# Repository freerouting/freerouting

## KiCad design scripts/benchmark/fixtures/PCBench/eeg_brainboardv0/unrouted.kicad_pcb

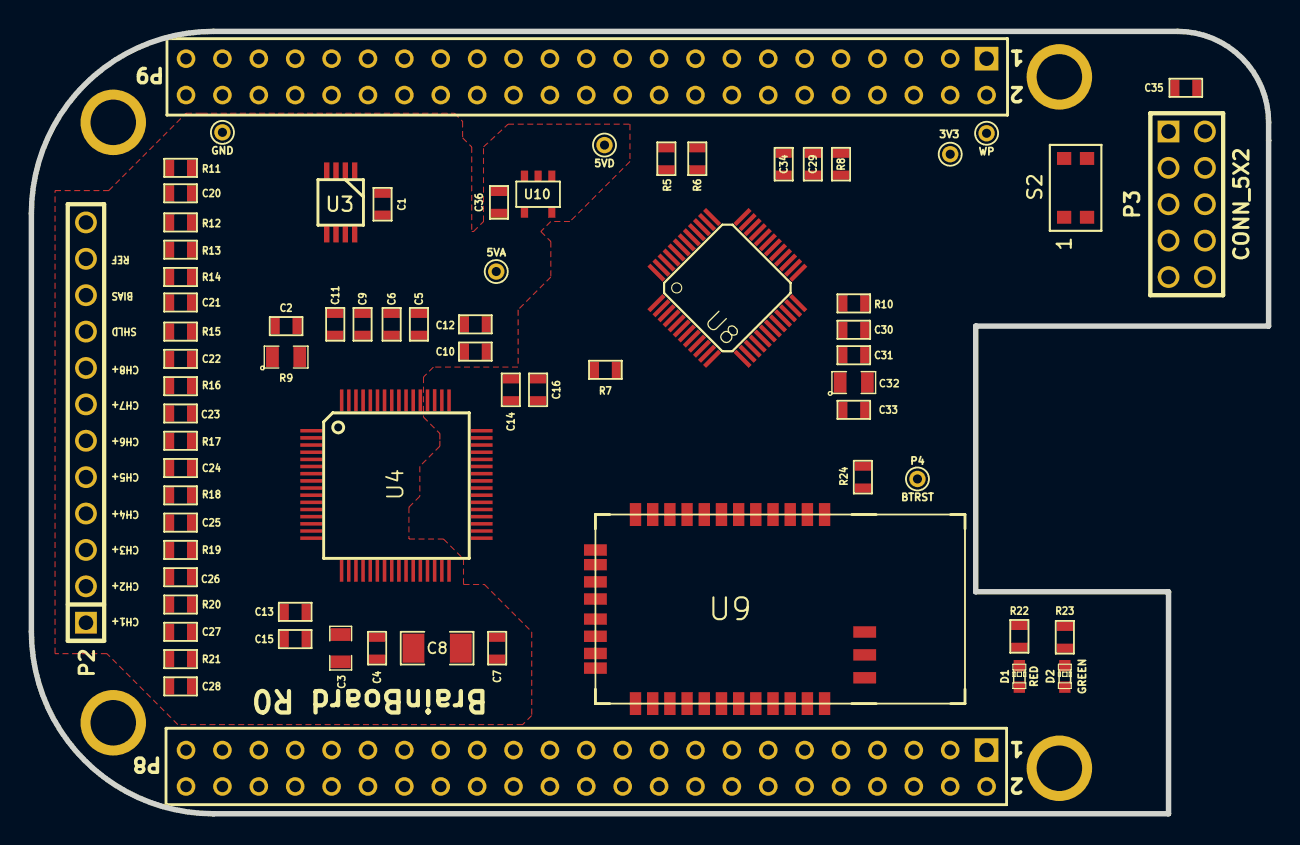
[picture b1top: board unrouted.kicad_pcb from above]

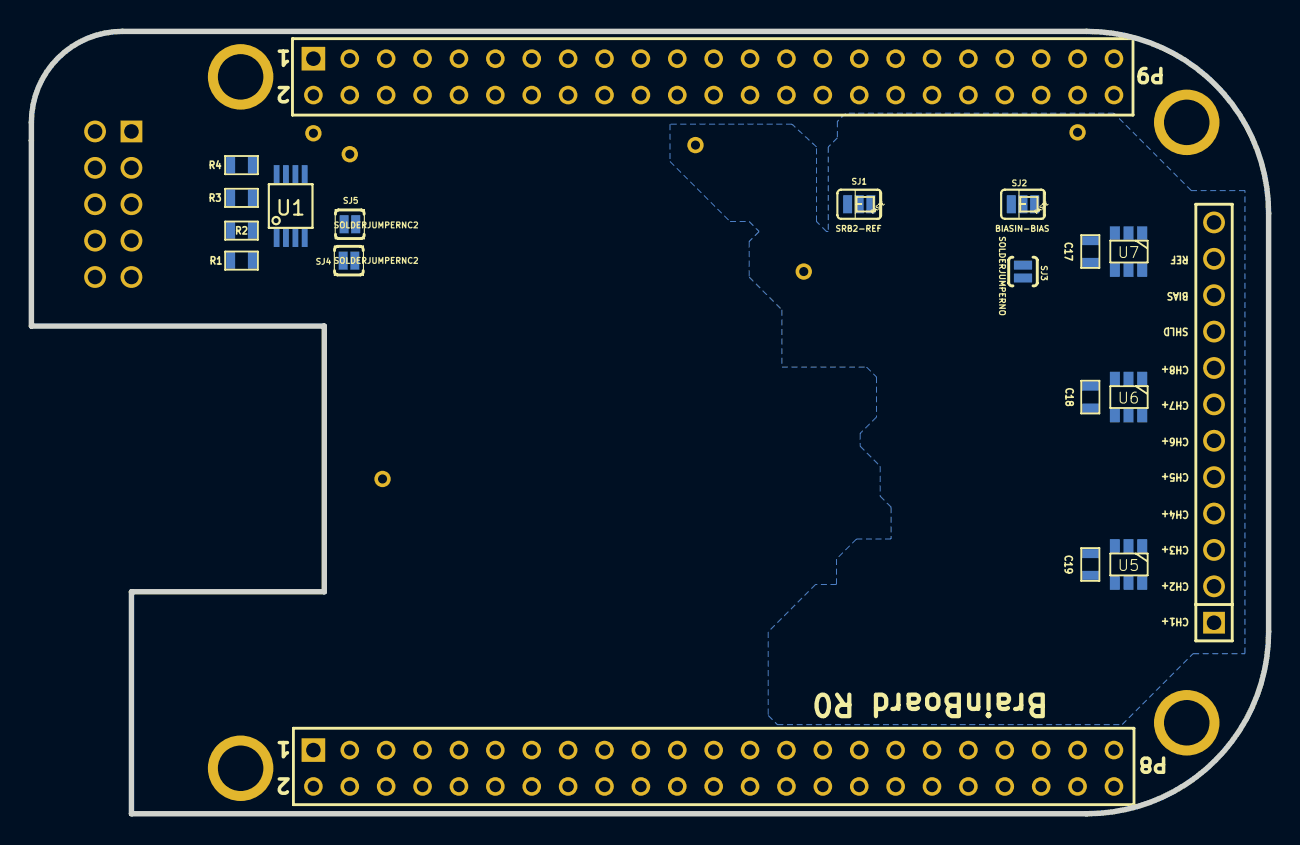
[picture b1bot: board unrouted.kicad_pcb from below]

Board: 4 copper layers, 86.4 x 54.6 mm, 86 parts (16 on the bottom side), 70 nets, no tracks yet.

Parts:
C1, C6, C11, C12, C15, C16, C17, C18, C19, C29, C31, C33, C34, C35, C36: 0.1uF; SM0603
C2: 1nF; SM0603
C3, C32: 10uF; SM0805
C4, C5, C7, C9, C10, C13, C14: 1uF; SM0603
C8: 100uF; SM1206
C20, C21, C22, C23, C24, C25, C26, C27, C28: 4.7nF; SM0603
C30: 2.2uF; SM0603
D1: RED; LED-0603
D2: GREEN; LED-0603
P1: WP; PINTST
P2: CONN_12; PIN_ARRAY-12X1
P3: CONN_5X2; PIN_ARRAY_5x2
P4: BTRST; PINTST
P5: GND; PINTST
P6: 5VD; PINTST
P7: 3V3; PINTST
P8: 5VA; PINTST
R1, R2, R3: 4.7K; SM0603
R4, R7, R8, R10, R24: 10K; SM0603
R5, R6: 5.6K; SM0603
R9: 499K,0.1%; SM0805
R11, R12, R13, R14, R15, R16, R17, R18, R19, R20, R21: 4.99K; SM0603
R22, R23: 330; SM0603
S2: SMT_BUTTON; KMR231GLFS
SJ1, SJ2: SOLDERJUMPER_2WAYPASTE2&3; SparkFun-Passives-SJ_3_PASTE2&3
SJ3: SOLDERJUMPERNO; SparkFun-Passives-SJ_2S-NO
SJ4, SJ5: SOLDERJUMPERNC2; SparkFun-Passives-SJ_2S-NOTRACE
U1: 24C256; SSOP8
U2: BEAGLEBONE_BLACK
U3: OPA2376; MSOP_8
U4: ADS1299; TQFP_64
U5, U6, U7: TPD4E001; SOT23_6
U8: ATUC3L064; -TQFP48
U9: BLUETOOTH-RN42; SparkFun-RF-RN41
U10: TPS73150; SOT23-5

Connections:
3V3: C14.1, C16.1, C29.1, C30.1, C31.1, C32.1, C33.1, C34.1, C35.1, P3.4, P7.1, R1.1, R2.1, R3.1, R4.1, R5.1, R6.1, R7.1, R8.1, R10.1, U1.8, U2.B3, U2.B4, U4.48, U4.50, U4.52, U8.17, U8.18, U8.34, U8.35, U8.42, U8.48, U9.11
+5VA: C1.1, C9.1, C10.1, C11.1, C12.1, C13.1, C15.1, C17.1, C18.1, C19.1, P8.1, U3.8, U4.19, U4.21, U4.22, U4.54, U4.56, U4.59, U5.6, U6.6, U7.6, U10.5
+5VD: P6.1, U2.B7, U2.B8, U10.1, U10.3
/A0: R3.2, U1.1
/A1: R2.2, SJ5.1, U1.2
/A2: R1.2, SJ4.1, U1.3
/BrainBoard AFE/BIASIN: SJ2.1, U4.62
/BrainBoard AFE/BIASINV: C2.1, R9.2, U4.61
/BrainBoard AFE/BIASOUT: C2.2, R9.1, SJ3.2, U4.63
/BrainBoard AFE/SRB1: U3.6, U3.7, U4.17
/BrainBoard AFE/SRB2: SJ1.1, U4.18
/BrainBoard AFE/VCAP1: C8.1, U4.28
/BrainBoard AFE/VCAP2: C7.1, U4.30
/BrainBoard AFE/VCAP3: C5.1, C6.1, U4.55
/BrainBoard AFE/VCAP4: C4.1, U4.26
/BrainBoard AFE/VREFP: C3.2, U4.24
/BrainBoard Analog In/BIAS_ELEC: P2.10, R12.1, U7.2
/BrainBoard Analog In/BIAS_SHD: P2.9, R13.1, U7.4
/BrainBoard Analog In/CH1ELEC_P: P2.1, R21.1, U5.4
/BrainBoard Analog In/CH2ELEC_P: P2.2, R20.1, U5.5
/BrainBoard Analog In/CH3ELEC_P: P2.3, R19.1, U5.1
/BrainBoard Analog In/CH4ELEC_P: P2.4, R18.1, U5.2
/BrainBoard Analog In/CH5ELEC_P: P2.5, R17.1, U6.4
/BrainBoard Analog In/CH6ELEC_P: P2.6, R16.1, U6.5
/BrainBoard Analog In/CH7ELEC_P: P2.7, R15.1, U6.1
/BrainBoard Analog In/CH8ELEC_P: P2.8, R14.1, U6.2
/BrainBoard Analog In/REF_ELEC: P2.11, R11.1, U7.1
/BrainBoard Bluetooth/FACTORY: P4.1, R24.1, U9.22
/BrainBoard Bluetooth/STATUS: D2.1, U9.19
/BrainBoard Bluetooth/STATUSn: D1.1, U9.21
/BrainBoard MCU/RESET_MCU: P3.6, U8.22
/BrainBoard MCU/TCK: P3.1, U8.11
/BrainBoard MCU/TDI: P3.9, U8.4
/BrainBoard MCU/TDO: P3.3, U8.13
/BrainBoard MCU/TMS: P3.5, U8.14
/CS: R7.2, U4.39, U8.6
/DRDY: U4.47, U8.31
/PWDN: R8.2, U4.35, U8.25
/RESET: R10.2, U4.36, U8.21
/SCL: R5.2, U1.6, U2.B19
/SDA: R6.2, U1.5, U2.B20
/WP: P1.1, R4.2, U1.7
AGND: C1.2, C3.1, C4.2, C5.2, C6.2, C7.2, C8.2, C9.2, C10.2, C11.2, C12.2, C13.2, C14.2, C15.2, C16.2, C17.2, C18.2, C19.2, C20.2, C21.2, C22.2, C23.2, C24.2, C25.2, C26.2, C27.2, C28.2, C29.2, C30.2, C31.2, C32.2, C33.2, C34.2, C35.2, C36.2, P3.2, P3.10, P5.1, R22.2, R23.2, R24.2, S2.1, S2.3, SJ4.2, SJ5.2, U1.4, U2.A1, U2.A2, U2.B1, U2.B2, U2.B34, U2.B43, U2.B44, U2.B45, U2.B46, U3.4, U4.20, U4.23, U4.25, U4.31, U4.32, U4.33, U4.49, U4.51, U4.53, U4.57, U4.58, U5.3, U6.3, U7.3, U8.1, U8.19, U8.33, U8.43, U8.45, U9.1, U9.12, U9.25, U9.27, U9.28, U9.29, U10.2
AIN1P: C28.1, R21.2, U4.16
AIN2P: C27.1, R20.2, U4.14
AIN3P: C26.1, R19.2, U4.12
AIN4P: C25.1, R18.2, U4.10
AIN5P: C24.1, R17.2, U4.8
AIN6P: C23.1, R16.2, U4.6
AIN7P: C22.1, R15.2, U4.4
AIN8P: C21.1, R14.2, U4.2
BIAS: R12.2, SJ2.3, U3.3
MISO: U4.43, U8.7
MOSI: U4.34, U8.8
unnamed: S2.2, S2.4, U2.B9
unnamed: SJ2.2, SJ3.1
unnamed: SJ1.2, U3.5
unnamed: D2.2, R23.1
unnamed: D1.2, R22.1
unnamed: C36.1, U10.4
REF: C20.1, R11.2, SJ1.3
RESET_BT: U8.30, U9.5
SCLK: U4.40, U8.16
SHIELD: R13.2, U3.1, U3.2
START: U4.38, U8.39
SYS_RESETn: U2.B10, U8.20
UARTBT_RX: U2.A37, U9.13
UARTBT_TX: U2.A38, U9.14
UARTUC_RX: U2.B13, U8.15
UARTUC_TX: U2.B11, U8.10

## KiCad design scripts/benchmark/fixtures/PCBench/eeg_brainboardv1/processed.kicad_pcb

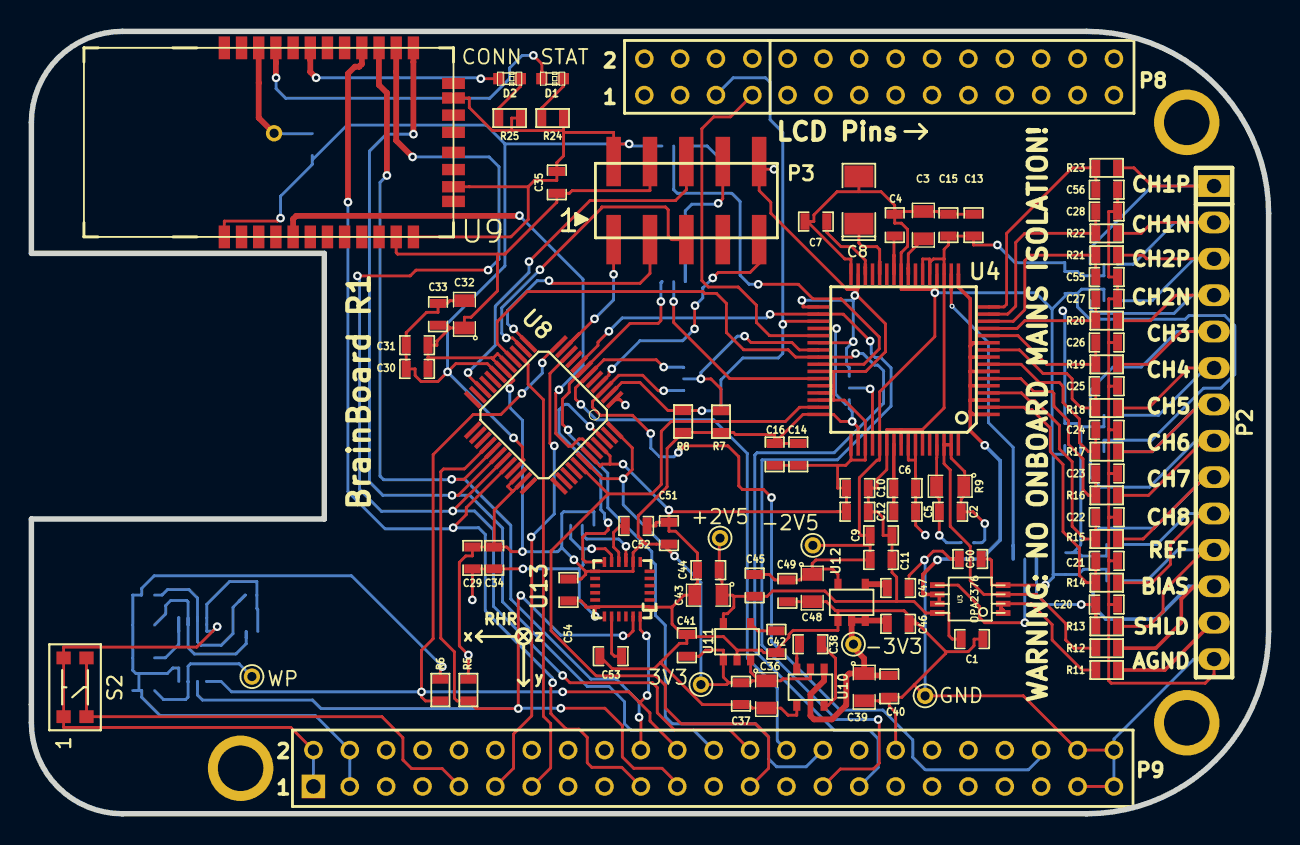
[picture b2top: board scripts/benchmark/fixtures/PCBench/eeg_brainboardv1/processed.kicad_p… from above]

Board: 4 copper layers, 86.4 x 54.6 mm, 116 parts (0 on the bottom side), 86 nets.

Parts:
C1, C6, C11, C12, C15, C16, C17, C18, C19, C29, C31, C33, C34, C35, C45, C50, C51, C52: 0.1uF; SM0603_Capa
C2: 1nF; SM0603_Capa
C3, C32, C36, C39, C43, C48: 10uF; SM0805
C4, C5, C7, C9, C10, C13, C14, C37, C38, C40, C41, C46: 1uF; SM0603_Capa
C8: 100uF; SM1206POL
C20, C21, C22, C23, C24, C25, C26, C27, C28, C55, C56: 4.7nF; SM0603_Capa
C30, C44, C49: 2.2uF; SM0603_Capa
C42, C47, C54: 0.01uF; SM0603_Capa
C53: 2.2nF; SM0603_Capa
D1: STAT; LED-0603
D2: CONN; LED-0603
P1: WP; PINTST
P2: CONN_14; pin_strip_14
P3: CONN_5X2; bb02-hp10
P4: BTRST; PINTST
P5: GND; PINTST
P6: -3V3; PINTST
P7: 3V3; PINTST
P8: +2V5; PINTST
P9: -2V5; PINTST
P10: CONN_2X2; bb02-hp04
R1, R2, R3: 4.7K; SM0603
R4, R7, R8, R26: 10K; SM0603
R5, R6: 5.6K; SM0603
R9: 499K,0.1%; SM0805
R11, R12, R13, R14, R15, R16, R17, R18, R19, R20, R21, R22, R23: 4.99K; SM0603
R24, R25: 330; SM0603
S2: SMT_BUTTON; KMR231GLFS
SJ1: REF-SRB2; SparkFun-Passives-SJ_3_PASTE2&3
SJ2, SJ7: DAISY_CS; SparkFun-Passives-SJ_3_PASTE2&3
SJ3: NO BIAS FILT; SparkFun-Passives-SJ_2S-NO
SJ4: A2; SparkFun-Passives-SJ_2S-NOTRACE
SJ5: A1; SparkFun-Passives-SJ_2S-NOTRACE
SJ6: DAISY_OUT; SparkFun-Passives-SJ_3_PASTE2&3
SJ8: CLKSEL; SparkFun-Passives-SJ_3_PASTE1&2
SJ9: I2C Address Select (2&3NC); SparkFun-Passives-SJ_3_PASTE2&3
U1: 24C256; SSOP8
U2: BEAGLEBONE_BLACK; BEAGLEBONE_BLACK_EEGMOD
U3: OPA2376; msoic-8
U4: ADS1299; TQFP_64
U5, U6, U7: TPD4E001DBV; SOT23_6
U8: ATUC3L064; -TQFP48
U9: BLUETOOTH-RN42; SparkFun-RF-RN41
U10: TPS60403; SOT23-5
U11: TPS73225; SOT23-5
U12: TPS72325; SOT23-5
U13: MPU6050; QFN24-4x4

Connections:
+2.5V: C1.1, C9.1, C10.1, C11.1, C12.1, C13.1, C15.1, C17.1, C18.1, C19.1, C43.1, C44.1, C45.1, P8.1, U3.8, U4.19, U4.21, U4.22, U4.54, U4.56, U4.59, U5.5, U6.5, U7.5, U11.5
+3.3V: C14.1, C16.1, C29.1, C30.1, C31.1, C32.1, C33.1, C34.1, C35.1, C36.1, C37.1, C41.1, C51.1, C54.1, P3.4, P7.1, R1.1, R2.1, R3.1, R4.1, R5.1, R6.1, R7.1, R8.1, SJ8.1, SJ9.1, U1.8, U2.B3, U2.B4, U4.36, U4.48, U4.50, U8.17, U8.18, U8.34, U8.35, U8.42, U8.48, U9.11, U10.2, U11.1, U11.3, U13.8, U13.13
-2.5V: C3.1, C4.2, C5.2, C6.2, C7.2, C8.2, C9.2, C11.2, C13.2, C15.2, C17.2, C18.2, C19.2, C45.2, C48.1, C49.1, C50.1, P9.1, U3.4, U4.20, U4.23, U4.25, U4.32, U4.53, U4.57, U4.58, U5.2, U6.2, U7.2, U12.5
-3.3V: C39.1, C40.1, C46.1, P6.1, U10.1, U12.2, U12.3
/A0: R3.2, U1.1
/A1: R2.2, SJ5.1, U1.2
/A2: R1.2, SJ4.1, U1.3
/BrainBoard AFE//CS: R7.2, SJ2.2, U4.39
/BrainBoard AFE/BIASINV: C2.1, R9.2, SJ3.1, U4.61
/BrainBoard AFE/CLKSEL: SJ8.2, U4.52
/BrainBoard AFE/DAISY: SJ7.2, U4.41
/BrainBoard AFE/DAISY_IN: P10.1, SJ7.1
/BrainBoard AFE/DOUT: SJ6.2, U4.43
/BrainBoard AFE/SRB1: U3.6, U3.7, U4.1, U4.3, U4.5, U4.7, U4.9, U4.11, U4.17
/BrainBoard AFE/SRB2: SJ1.1, U4.18
/BrainBoard AFE/VCAP1: C8.1, U4.28
/BrainBoard AFE/VCAP2: C7.1, U4.30
/BrainBoard AFE/VCAP3: C5.1, C6.1, U4.55
/BrainBoard AFE/VCAP4: C4.1, U4.26
/BrainBoard AFE/VREFP: C3.2, U4.24
/BrainBoard Analog In/BIAS_ELEC: P2.12, R12.1, U7.3
/BrainBoard Analog In/BIAS_SHD: P2.13, R11.1
/BrainBoard Analog In/CH1ELEC_N: P2.2, R22.1, U5.6
/BrainBoard Analog In/CH1ELEC_P: P2.1, R23.1, U5.4
/BrainBoard Analog In/CH2ELEC_N: P2.4, R20.1, U5.3
/BrainBoard Analog In/CH2ELEC_P: P2.3, R21.1, U5.1
/BrainBoard Analog In/CH3ELEC_P: P2.5, R19.1, U6.4
/BrainBoard Analog In/CH4ELEC_P: P2.6, R18.1, U6.6
/BrainBoard Analog In/CH5ELEC_P: P2.7, R17.1, U6.1
/BrainBoard Analog In/CH6ELEC_P: P2.8, R16.1, U6.3
/BrainBoard Analog In/CH7ELEC_P: P2.9, R15.1, U7.4
/BrainBoard Analog In/CH8ELEC_P: P2.10, R14.1, U7.6
/BrainBoard Analog In/REF_ELEC: P2.11, R13.1, U7.1
/BrainBoard Bluetooth/FACTORY: P4.1, R26.1, U9.22
/BrainBoard Bluetooth/STATUS: D2.1, U9.19
/BrainBoard Bluetooth/STATUSn: D1.1, U9.21
/BrainBoard IMU/AD0: SJ9.2, U13.9
/BrainBoard IMU/CPOUT: C53.1, U13.20
/BrainBoard IMU/REGOUT: C52.1, U13.10
/BrainBoard MCU/RESET_MCU: P3.6, U8.22
/BrainBoard MCU/TCK: P3.1, U8.11
/BrainBoard MCU/TDI: P3.9, U8.4
/BrainBoard MCU/TDO: P3.3, U8.13
/BrainBoard MCU/TMS: P3.5, U8.14
/CS_DAISY: SJ2.1, U2.B42, U8.3
/CS_MAIN: SJ2.3, U2.B28, U8.6
/DRDY: U2.B25, U4.47, U8.41
/PWDN: R8.2, U2.A23, U4.35, U8.2
/WP: P1.1, R4.2, U1.7
AGND: C1.2, C10.2, C12.2, C14.2, C16.2, C20.2, C21.2, C22.2, C23.2, C24.2, C25.2, C26.2, C27.2, C28.2, C29.2, C30.2, C31.2, C32.2, C33.2, C34.2, C35.2, C36.2, C37.2, C39.2, C40.2, C41.2, C42.2, C43.2, C44.2, C46.2, C47.2, C48.2, C49.2, C50.2, C51.2, C52.2, C53.2, C54.2, C55.2, C56.2, P2.14, P3.2, P3.10, P5.1, R24.2, R25.2, R26.2, S2.1, S2.3, SJ4.2, SJ5.2, SJ7.3, SJ8.3, SJ9.3, U1.4, U2.B1, U2.B2, U2.B34, U2.B43, U2.B44, U2.B45, U2.B46, U4.31, U4.33, U4.38, U4.42, U4.44, U4.45, U4.46, U4.49, U4.51, U8.1, U8.19, U8.33, U8.43, U8.45, U9.1, U9.12, U9.28, U9.29, U10.4, U11.2, U12.1, U13.1, U13.11, U13.18
AIN1N: C28.1, R22.2, U4.15
AIN1P: C56.1, R23.2, U4.16
AIN2N: C27.1, R20.2, U4.13
AIN2P: C55.1, R21.2, U4.14
AIN3P: C26.1, R19.2, U4.12
AIN4P: C25.1, R18.2, U4.10
AIN5P: C24.1, R17.2, U4.8
AIN6P: C23.1, R16.2, U4.6
AIN7P: C22.1, R15.2, U4.4
AIN8P: C21.1, R14.2, U4.2
BIAS: C2.2, R9.1, R12.2, SJ3.2, U3.3, U4.62, U4.63
CLK: U2.A25, U4.37
DAISY_OUT: P3.8, SJ6.1
I2C2_SCL: R5.2, U1.6, U2.B21, U8.28, U13.23
I2C2_SDA: R6.2, U1.5, U2.B22, U8.12, U13.24
IMU_INT: U8.46, U13.12
MISO: SJ6.3, U2.B30, U8.7
MOSI: U2.B29, U4.34, U8.8
unnamed: S2.2, S2.4, U2.B9
unnamed: D2.2, R25.1
unnamed: D1.2, R24.1
unnamed: C47.1, U12.4
unnamed: C38.1, U10.5
unnamed: C38.2, U10.3
unnamed: C42.1, U11.4
unnamed: SJ1.2, U3.5
REF: C20.1, R13.2, SJ1.3
RESET_BT: U8.44, U9.5
SCLK: U2.B31, U4.40, U8.16
SHIELD: R11.2, U3.1, U3.2
UARTBT_CTS: U2.B20, U8.29, U9.15
UARTBT_RTS: U2.B19, U8.32, U9.16
UARTBT_RX: U2.B26, U8.31, U9.14
UARTBT_TX: U2.B24, U8.30, U9.13
UARTUC_RX: U2.B13, U8.15
UARTUC_TX: U2.B11, U8.10

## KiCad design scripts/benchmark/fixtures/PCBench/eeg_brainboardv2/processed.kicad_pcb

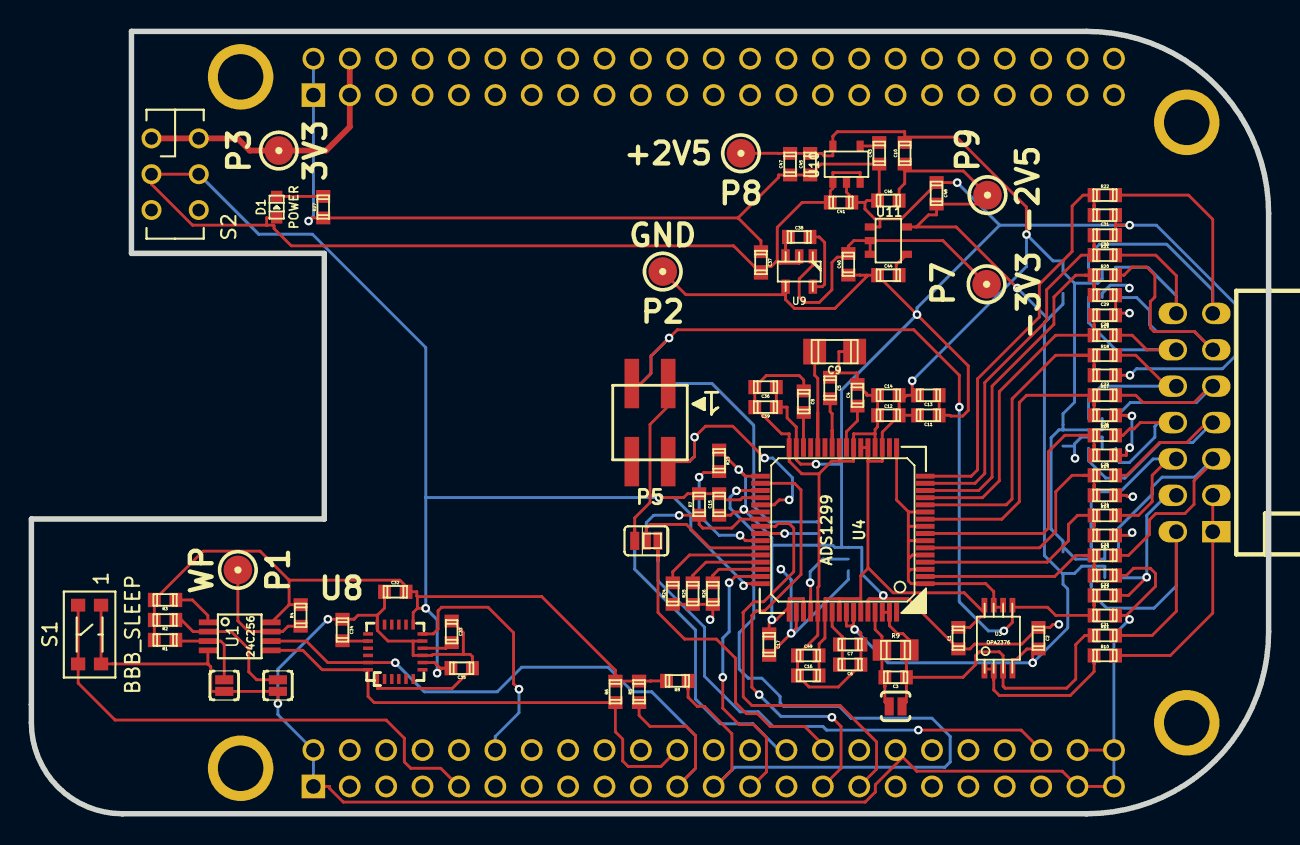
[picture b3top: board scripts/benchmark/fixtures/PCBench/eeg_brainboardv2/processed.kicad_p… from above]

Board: 4 copper layers, 86.4 x 54.6 mm, 105 parts (0 on the bottom side), 72 nets.

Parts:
C1, C2, C7, C12, C13, C16, C17, C18, C19, C20, C32, C33, C39, C49: 0.1uF; c_0603
C3: 1nF; c_0603
C4, C45, C46: 10uF; c_0603
C5, C6, C8, C10, C11, C14, C15, C36, C37, C38, C40, C41: 1uF; c_0603
C9: 100uF; c_1206
C21, C22, C23, C24, C25, C26, C27, C28, C29, C30, C31: 4.7nF; c_0603
C34: 2.2nF; c_0603
C35, C43, C44: 0.01uF; c_0603
C47, C48: 2.2uF; c_0603
D1: POWER; Led_0603
P1: WP; testpoint_2mm
P2: GND; testpoint_2mm
P3: 3V3; testpoint_2mm
P4: DAISY_IN_CONN; bb02-hp04
P5: DAISY_OUT_CONN; bb02-hp04
P6: CONN_14; pin_socket_7x2-90
P7: -3V3; testpoint_2mm
P8: +2V5; testpoint_2mm
P9: -2V5; testpoint_2mm
R1, R2, R3: 4.7K; r_0603
R4, R7, R8, R23, R24, R25, R26: 10K; r_0603
R5, R6: 5.6K; r_0603
R9: 499K,0.1%; r_0805
R10, R11, R12, R13, R14, R15, R16, R17, R18, R19, R20, R21, R22: 4.99K; r_0603
R27: 330; r_0603
S1: BBB_SLEEP; KMR231GLFS
S2: DPDT; JS202011AQN
SJ1: A2; SparkFun-Passives-SJ_2S-NOTRACE
SJ2: A1; SparkFun-Passives-SJ_2S-NOTRACE
SJ3, SJ6: DAISY_CS; SparkFun-Passives-SJ_3_PASTE2&3
SJ4: DAISY_OUT; SparkFun-Passives-SJ_3_PASTE2&3
SJ5: NO BIAS FILT; SparkFun-Passives-SJ_2S-NO
SJ7: CLKSEL; SparkFun-Passives-SJ_3_PASTE1&2
U1: 24C256; SSOP-8
U2: BEAGLEBONE_BLACK
U3: OPA2376; msoic-8
U4: ADS1299; lqfp64
U5, U6, U7: TPD4E001DBV; sot23-6
U8: MPU6050; QFN24-4x4
U9: TPS60403; sot23-5
U10: TPS73225; SOT23-5
U11: TPS72325; SOT23-5

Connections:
+2.5V: C1.1, C10.1, C11.1, C12.1, C13.1, C14.1, C16.1, C18.1, C19.1, C20.1, C45.1, C47.1, C49.1, P8.1, U3.8, U4.19, U4.21, U4.22, U4.54, U4.56, U4.59, U5.5, U6.5, U7.5, U10.5
+3.3V: C15.1, C17.1, C32.1, C35.1, C37.1, C41.1, D1.1, R1.1, R2.1, R3.1, R4.1, R5.1, R6.1, R7.1, R8.1, S2.2, S2.5, SJ7.1, U1.8, U4.36, U4.48, U4.50, U8.8, U8.13, U9.2, U10.1, U10.3
-2.5V: C2.1, C4.1, C5.2, C6.2, C7.2, C8.2, C9.2, C10.2, C12.2, C14.2, C16.2, C18.2, C19.2, C20.2, C36.1, C39.1, C46.1, C48.1, C49.2, P9.1, U3.4, U4.20, U4.23, U4.25, U4.32, U4.53, U4.57, U4.58, U5.2, U6.2, U7.2, U11.5
-3.3V: C40.1, P7.1, U9.1, U11.2, U11.3
/A0: R3.2, U1.1
/A1: R2.2, SJ2.1, U1.2
/A2: R1.2, SJ1.1, U1.3
/Brainboard AFE//CS: R7.2, SJ3.2, U4.39
/Brainboard AFE/BIASINV: C3.1, R9.2, SJ5.1, U4.61
/Brainboard AFE/CLKSEL: SJ7.2, U4.52
/Brainboard AFE/DAISY: SJ6.2, U4.41
/Brainboard AFE/DAISY_IN: P4.2, SJ6.1
/Brainboard AFE/DOUT: SJ4.2, U4.43
/Brainboard AFE/SRB1: U3.6, U3.7, U4.1, U4.3, U4.5, U4.7, U4.9, U4.11, U4.17
/Brainboard AFE/VCAP1: C9.1, U4.28
/Brainboard AFE/VCAP2: C8.1, U4.30
/Brainboard AFE/VCAP3: C6.1, C7.1, U4.55
/Brainboard AFE/VCAP4: C5.1, U4.26
/Brainboard AFE/VREFP: C4.2, U4.24
/Brainboard Analog In/BIAS_ELEC: P6.2, R11.1, U7.3
/Brainboard Analog In/BIAS_SHD: P6.1, P6.3, R10.1
/Brainboard Analog In/CH1ELEC_N: P6.14, R21.1, U5.6
/Brainboard Analog In/CH1ELEC_P: P6.13, R22.1, U5.4
/Brainboard Analog In/CH2ELEC_N: P6.12, R19.1, U5.3
/Brainboard Analog In/CH2ELEC_P: P6.11, R20.1, U5.1
/Brainboard Analog In/CH3ELEC_P: P6.10, R18.1, U6.4
/Brainboard Analog In/CH4ELEC_P: P6.9, R17.1, U6.6
/Brainboard Analog In/CH5ELEC_P: P6.8, R16.1, U6.1
/Brainboard Analog In/CH6ELEC_P: P6.7, R15.1, U6.3
/Brainboard Analog In/CH7ELEC_P: P6.6, R14.1, U7.4
/Brainboard Analog In/CH8ELEC_P: P6.5, R13.1, U7.6
/Brainboard Analog In/REF_ELEC: P6.4, R12.1, U7.1
/Brainboard IMU/CPOUT: C34.1, U8.20
/Brainboard IMU/REGOUT: C33.1, U8.10
/CS_DAISY: SJ3.1, U2.B42
/CS_MAIN: SJ3.3, U2.B28
/DRDY: U2.B25, U4.47
/PWDN: R8.2, U2.B23, U4.35
/WP: P1.1, R4.2, U1.7
AGND: C1.2, C2.2, C11.2, C13.2, C15.2, C17.2, C21.2, C22.2, C23.2, C24.2, C25.2, C26.2, C27.2, C28.2, C29.2, C30.2, C31.2, C32.2, C33.2, C34.2, C35.2, C36.2, C37.2, C39.2, C40.2, C41.2, C43.2, C44.2, C45.2, C46.2, C47.2, C48.2, P2.1, R23.2, R24.2, R25.2, R26.2, R27.2, S1.1, S1.3, SJ1.2, SJ2.2, SJ6.3, SJ7.3, U1.4, U2.A1, U2.A2, U2.B1, U2.B2, U2.B34, U2.B43, U2.B44, U2.B45, U2.B46, U4.31, U4.33, U4.38, U4.49, U4.51, U4.60, U8.1, U8.9, U8.11, U8.18, U9.4, U10.2, U11.1
AIN1N: C30.1, R21.2, U4.15
AIN1P: C31.1, R22.2, U4.16
AIN2N: C28.1, R19.2, U4.13
AIN2P: C29.1, R20.2, U4.14
AIN3P: C27.1, R18.2, U4.12
AIN4P: C26.1, R17.2, U4.10
AIN5P: C25.1, R16.2, U4.8
AIN6P: C24.1, R15.2, U4.6
AIN7P: C23.1, R14.2, U4.4
AIN8P: C22.1, R13.2, U4.2
BIAS: C3.2, R9.1, R11.2, SJ5.2, U3.3, U4.62, U4.63
CLK: P4.1, P5.2, U4.37
DAISY_OUT: P5.1, SJ4.1
I2C2_SCL: R5.2, U1.6, U2.B21, U8.23
I2C2_SDA: R6.2, U1.5, U2.B22, U8.24
IMU_INT: U2.B12, U8.12
MISO: SJ4.3, U2.B30
MOSI: U2.B29, U4.34
unnamed: S1.2, S1.4, U2.B9
unnamed: R23.1, U4.42
unnamed: R24.1, U4.44
unnamed: R25.1, U4.45
unnamed: R26.1, U4.46
unnamed: C44.1, U11.4
unnamed: C43.1, U10.4
unnamed: D1.2, R27.1
unnamed: C38.1, U9.5
unnamed: C38.2, U9.3
REF_IN: C21.1, P4.4, P5.3, R12.2, U3.5
SCLK: U2.B31, U4.40
SHIELD: R10.2, U3.1, U3.2
VCC: P3.1, S2.1, S2.4, U2.A3, U2.A4

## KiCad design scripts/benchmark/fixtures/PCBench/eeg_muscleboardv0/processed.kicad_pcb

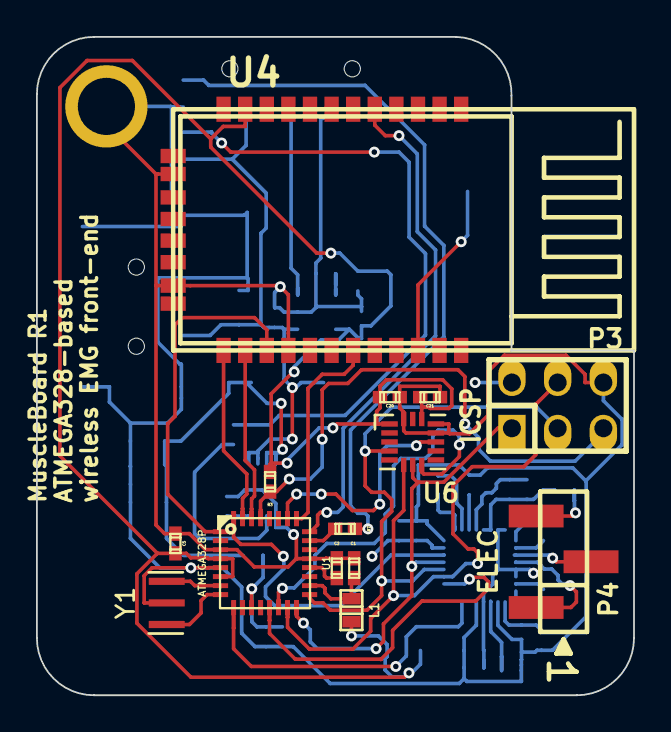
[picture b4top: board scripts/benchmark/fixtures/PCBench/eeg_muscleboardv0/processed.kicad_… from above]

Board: 4 copper layers, 33.2 x 36.6 mm, 54 parts (0 on the bottom side), 47 nets.

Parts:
C1, C2, C3, C5, C9, C15, C20, C21, C23, C25: 0.1uF; c_0402
C4, C8: 4.7uF; c_0805
C10: 0.01uF; c_0402
C11, C16: 10uF; c_0603
C12: 2.2uF; c_0402
C13, C14: 4.7nF; c_0402
C17, C18, C22, C24: 1uF; c_0402
C19: 1.5nF; c_0402
D1: CHG; Led_0603
D2: LSM115JE3/TR13; do214aa
D3: RED; Led_0603
FB1: BLM18PG121SN1; inductor_smd_0603
L1: 10uH; inductor_smd_0603
MTG1: MHOLE; BBB_MHOLE
P1: BATT; s2b-ph-sm4-tb
P2: USB; USB_MINI_B
P3: ICSP; pin_strip_3x2
P4: ELEC; bb02-hy03a
R1: 2.2M; r_0402
R2, R12: 1M; r_0402
R3, R5, R9, R10: 10k; r_0402
R4, R7: 2.2k; r_0402
R8: 51k; r_0402
S2: CHG/ON; JS102011SAQN
TP1: GND; testpoint_1mm5
TP2: 3V3; testpoint_1mm5
TP3: FACT; testpoint_1mm5
U1: ATMEGA328P; pvqfn-n32-nopad
U2: MCP73831T-DFN; dfn8-2x3
U3: TPS73233; sot23-5
U4: BLUETOOTH-RN42; roving_rn-42
U5: ADS1291; s-pvqfn-n32-nopad
U6: ADXL362; 16-LGA-3x3.25
Y1: RESONATOR; smd_resonator_1206

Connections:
+3.3V: C5.1, C11.1, C12.1, C20.1, C21.1, C24.1, C25.1, FB1.1, L1.2, P3.2, R3.1, TP2.1, U1.4, U1.6, U3.5, U4.11, U5.23, U6.1, U6.14
+BATT: C4.1, D2.1, P1.1, R1.1, U2.3, U2.4
/AREF: C2.1, U1.20
/AVCC: C1.1, L1.1, U1.18
/Analog front-end/GPIO1: R9.1, U5.26
/Analog front-end/GPIO2: R10.1, U5.25
/Analog front-end/PGA1N: C13.2, U5.1
/Analog front-end/PGA1P: C13.1, U5.2
/Analog front-end/PGA2N: C14.2, U5.7
/Analog front-end/PGA2P: C14.1, U5.8
/Analog front-end/RLDIN: C19.1, R8.1, R12.1, U5.29, U5.30
/Analog front-end/RLDINV: C19.2, R12.2, U5.28
/Analog front-end/VCAP1: C18.1, U5.11
/Analog front-end/VCAP2: C17.1, U5.27
/Analog front-end/VREFP: C15.1, C16.1, U5.9
/BATT_MON: C3.1, R1.2, R2.1, U1.11
/BT_CONN: U1.25, U4.19
/BT_RESET: U1.24, U4.5
/FACTORY_RESET: TP3.1, U4.22
/MCU_RX: U1.30, U4.14
/MCU_TX: U1.31, U4.13
/USER_LED: R7.2, U1.23
/~MCU_CTS: U1.1, U4.15
CH1N: P4.2, U5.3
CH1P: P4.1, U5.4
GND: C1.2, C2.2, C3.2, C4.2, C5.2, C8.2, C9.2, C10.2, C11.2, C12.2, C15.2, C16.2, C17.2, C18.2, C20.2, C21.2, C22.2, C23.2, C24.2, C25.2, D3.2, MTG1.1, P1.2, P2.5, P2.6, P2.7, P2.8, P2.9, P3.6, R2.2, R5.2, R9.2, R10.2, S2.3, TP1.1, U1.3, U1.5, U1.21, U2.5, U2.9, U3.2, U4.16, U4.28, U4.29, U5.10, U5.13, U5.24, U6.12, U6.13, U6.16, Y1.2
MISO: P3.1, U1.16, U5.21, U6.7
MOSI: P3.4, U1.15, U5.19, U6.6
unnamed: D3.1, R7.1
unnamed: U1.8, Y1.3
unnamed: U1.7, Y1.1
unnamed: R5.1, U2.8
unnamed: C10.1, U3.4
unnamed: S2.2, U3.3
unnamed: R4.2, U2.6
unnamed: D1.2, R4.1
unnamed: C22.1, C23.1
unnamed: U5.5, U5.6, U5.12, U5.31, U5.32
RLD: P4.3, R8.2
SCLK: P3.3, U1.17, U5.20, U6.4
VBUS: C8.1, C9.1, D1.1, D2.2, P2.1, S2.1, U2.1, U2.2, U3.1
XL_INT1: U1.26, U6.11
~AFE_CS: U1.13, U5.18
~AFE_DRDY: U1.32, U5.22
~AFE_PWDN: U1.9, U5.15
~MCU_RESET: P3.5, R3.2, U1.29
~XL_CS: U1.14, U6.8
